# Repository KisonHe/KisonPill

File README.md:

# KisonPill

Use the switch at the bottom to choose serial download from cp2102 on board or ft2232.
R1 should be left not connected.

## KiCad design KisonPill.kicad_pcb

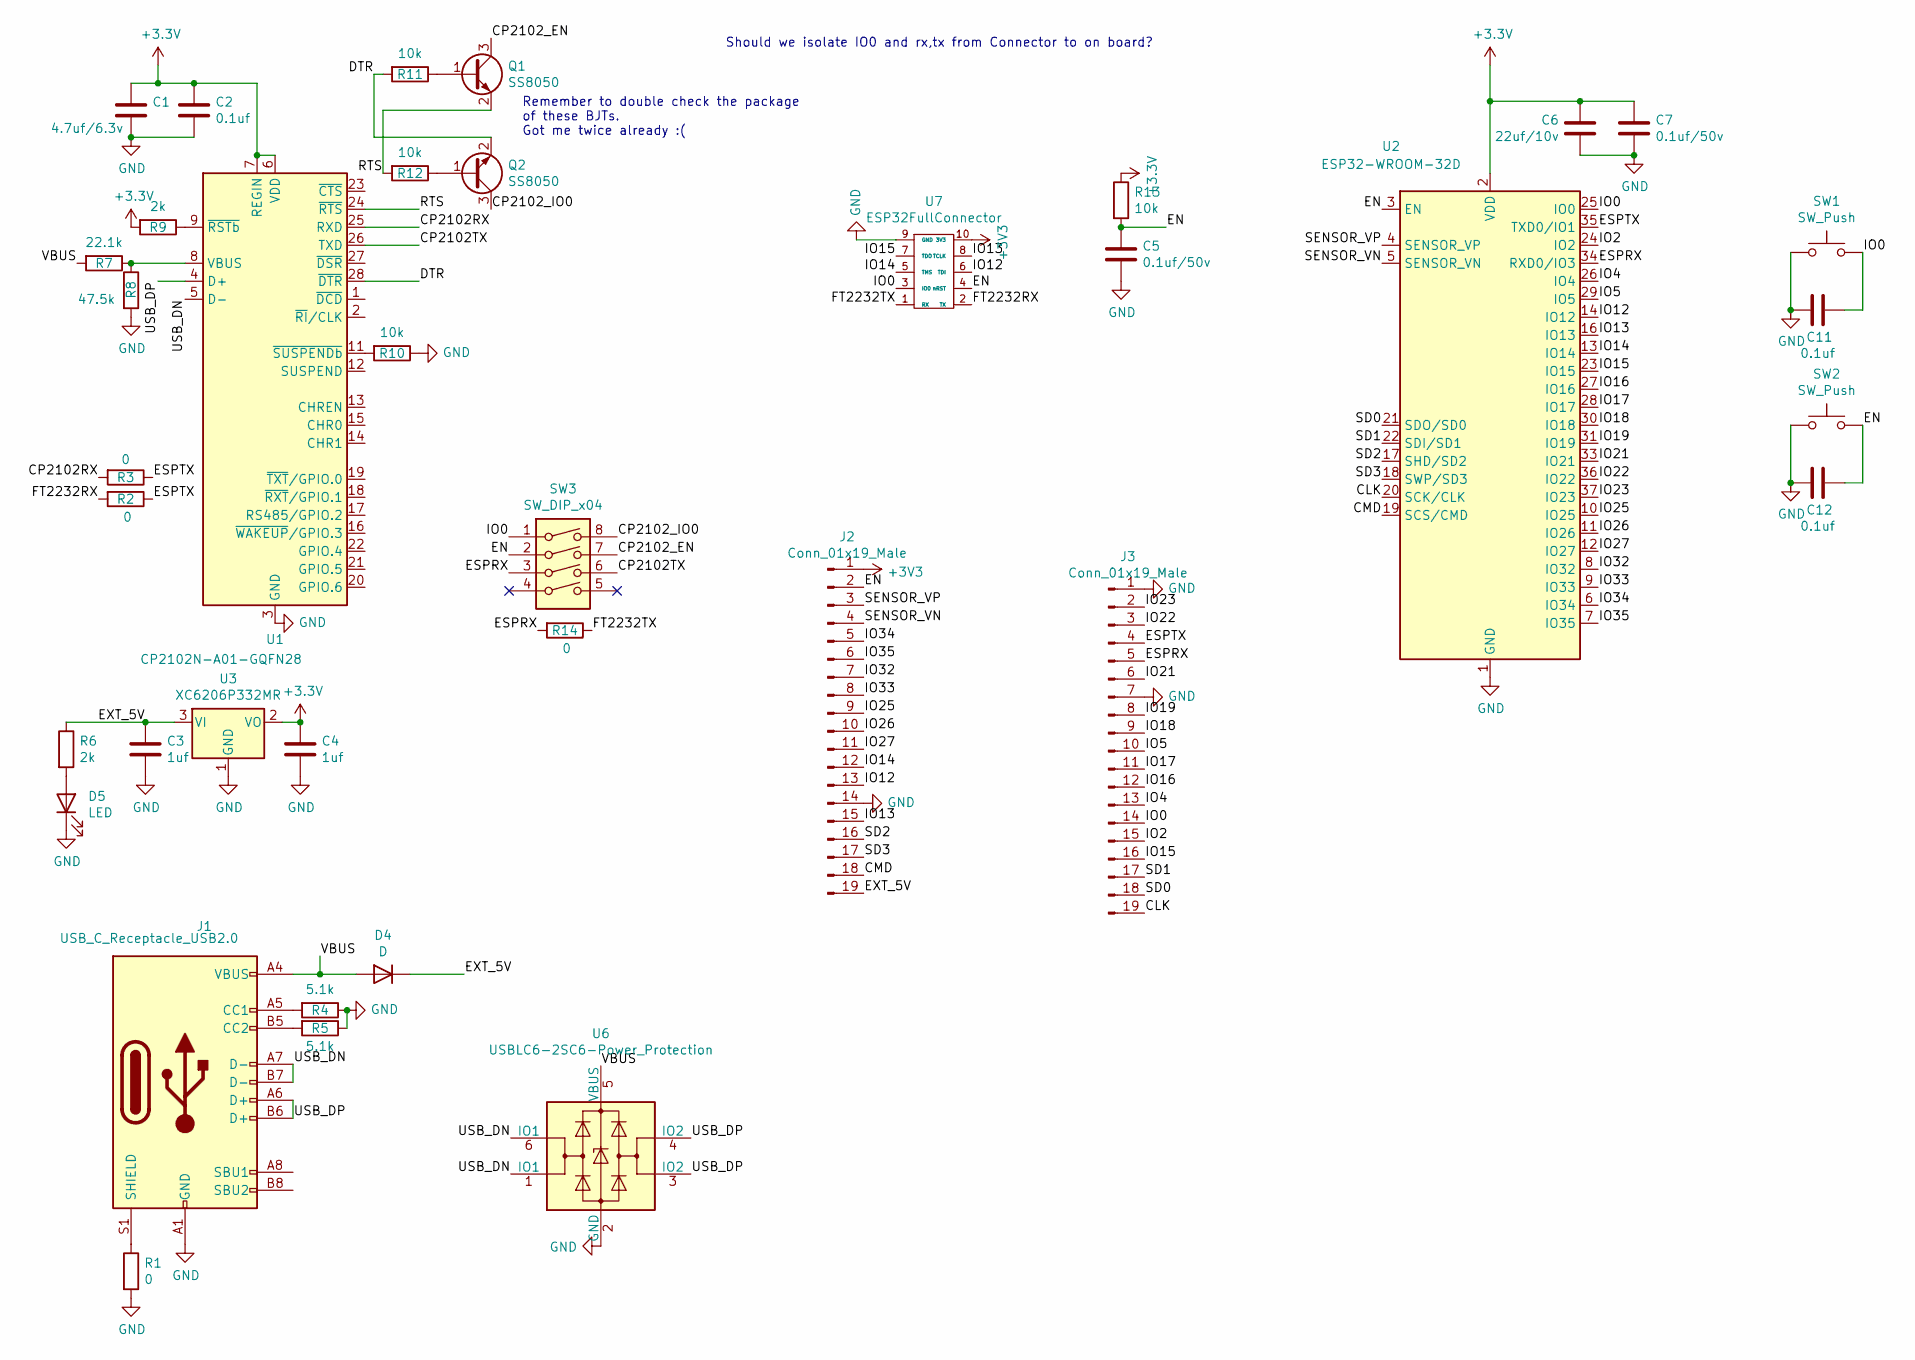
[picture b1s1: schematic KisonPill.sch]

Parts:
C1: 4.7uf/6.3v; C_0603_1608Metric; LCSC C907730
C2, C11, C12: 0.1uf; C_0603_1608Metric; LCSC C1688
C3, C4: 1uf; C_0603_1608Metric
C5, C7: 0.1uf/50v; C_0603_1608Metric; LCSC C1688
C6: 22uf/10v; C_1206_3216Metric; LCSC C319197
D4: D; D_SOD-323; LCSC C124187
D5: LED; LED_0603_1608Metric; LCSC C181863
J1: USB_C_Receptacle_USB2.0; USB_C_Receptacle_HRO_TYPE-C-31-M-12; LCSC C165948
J2, J3: Conn_01x19_Male; PinHeader_1x19_P2.54mm_Vertical
Q1, Q2: SS8050; SOT-23; LCSC C541705
R1, R2, R3, R14: 0; R_0603_1608Metric; LCSC C429667
R4, R5: 5.1k; R_0603_1608Metric; LCSC C325524
R6, R9: 2k; R_0603_1608Metric; LCSC C226705
R7: 22.1k; R_0603_1608Metric; LCSC C325588
R8: 47.5k; R_0603_1608Metric; LCSC C25896
R10, R11, R12, R13: 10k; R_0603_1608Metric; LCSC C149898
SW1, SW2: SW_Push; BTN-TS342A4P-WZ-C557592; LCSC C557592
SW3: SW_DIP_x04; SW_DIP_SPSTx04_Slide_Copal_CHS-04B_W7.62mm_P1.27mm
U1: CP2102N-A01-GQFN28; QFN-28-1EP_5x5mm_P0.5mm_EP3.35x3.35mm
U2: ESP32-WROOM-32D; ESP32-WROOM-32
U3: XC6206P332MR; SOT-23
U6: USBLC6-2SC6-Power_Protection; USBLC6-2P6-SOT666
U7: ESP32FullConnector; Molex_CLIK-Mate_502382-1070_1x10-1MP_P1.25mm_Vertical

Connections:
/CLK: J3.19, U2.20 (SCK/CLK)
/CMD: J2.18, U2.19 (SCS/CMD)
/CP2102RX: R3.2, U1.25 (RXD)
/CP2102TX: SW3.6, U1.26 (TXD)
/CP2102_EN: Q1.3 (C), SW3.7
/CP2102_IO0: Q2.3 (C), SW3.8
/DTR: Q2.2 (E), R11.2, U1.28 (~DTR)
/EN: C5.1, C12.2, J2.2, R13.2, SW2.2, SW3.2, U2.3 (EN), U7.4 (nRST)
/ESPRX: J3.5, R14.2, SW3.3, U2.34 (RXD0/IO3)
/ESPTX: J3.4, R2.1, R3.1, U2.35 (TXD0/IO1)
/EXT_5V: C3.1, D4.1 (K), J2.19, R6.1, U3.3 (VI)
/FT2232RX: R2.2, U7.2 (TX)
/FT2232TX: R14.1, U7.1 (RX)
/IO0: C11.2, J3.14, SW1.2, SW3.1, U2.25 (IO0), U7.3 (IO0)
/IO2: J3.15, U2.24 (IO2)
/IO4: J3.13, U2.26 (IO4)
/IO5: J3.10, U2.29 (IO5)
/IO12: J2.13, U2.14 (IO12), U7.6 (TDI)
/IO13: J2.15, U2.16 (IO13), U7.8 (TCLK)
/IO14: J2.12, U2.13 (IO14), U7.5 (TMS)
/IO15: J3.16, U2.23 (IO15), U7.7 (TDO)
/IO16: J3.12, U2.27 (IO16)
/IO17: J3.11, U2.28 (IO17)
/IO18: J3.9, U2.30 (IO18)
/IO19: J3.8, U2.31 (IO19)
/IO21: J3.6, U2.33 (IO21)
/IO22: J3.3, U2.36 (IO22)
/IO23: J3.2, U2.37 (IO23)
/IO25: J2.9, U2.10 (IO25)
/IO26: J2.10, U2.11 (IO26)
/IO27: J2.11, U2.12 (IO27)
/IO32: J2.7, U2.8 (IO32)
/IO33: J2.8, U2.9 (IO33)
/IO34: J2.5, U2.6 (IO34)
/IO35: J2.6, U2.7 (IO35)
/RTS: Q1.2 (E), R12.2, U1.24 (~RTS)
/SD0: J3.18, U2.21 (SDO/SD0)
/SD1: J3.17, U2.22 (SDI/SD1)
/SD2: J2.16, U2.17 (SHD/SD2)
/SD3: J2.17, U2.18 (SWP/SD3)
/SENSOR_VN: J2.4, U2.5 (SENSOR_VN)
/SENSOR_VP: J2.3, U2.4 (SENSOR_VP)
/USB_DN: J1.A7 (D-), J1.B7 (D-), U1.5 (D-), U6.1 (IO1), U6.6 (IO1)
/USB_DP: J1.A6 (D+), J1.B6 (D+), U1.4 (D+), U6.3 (IO2), U6.4 (IO2)
/VBUS: D4.2 (A), J1.A4 (VBUS), J1.A9 (VBUS), J1.B4 (VBUS), J1.B9 (VBUS), R7.2, U6.5 (VBUS)
GND: C1.2, C2.2, C3.2, C4.2, C5.2, C6.1, C7.2, C11.1, C12.1, D5.1 (K), J1.A1 (GND), J1.A12 (GND), J1.B1 (GND), J1.B12 (GND), J2.14, J3.1, J3.7, R1.2, R4.1, R5.1, R8.2, R10.1, SW1.1, SW2.1, U1.3 (GND), U1.29 (GND), U2.1 (GND), U2.15 (GND), U2.38 (GND), U2.39 (GND), U3.1 (GND), U6.2 (GND), U7.9 (GND)
unnamed: D5.2 (A), R6.2
unnamed: J1.A5 (CC1), R4.2
unnamed: J1.B5 (CC2), R5.2
unnamed: J1.S1 (SHIELD), R1.1
unnamed: Q1.1 (B), R11.1
unnamed: Q2.1 (B), R12.1
unnamed: R7.1, R8.1, U1.8 (VBUS)
unnamed: R9.1, U1.9 (~RSTb)
unnamed: R10.2, U1.11 (~SUSPENDb)

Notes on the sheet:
Should we isolate IO0 and rx,tx from Connector to on board?
Remember to double check the package of these BJTs. Got me twice already :(

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
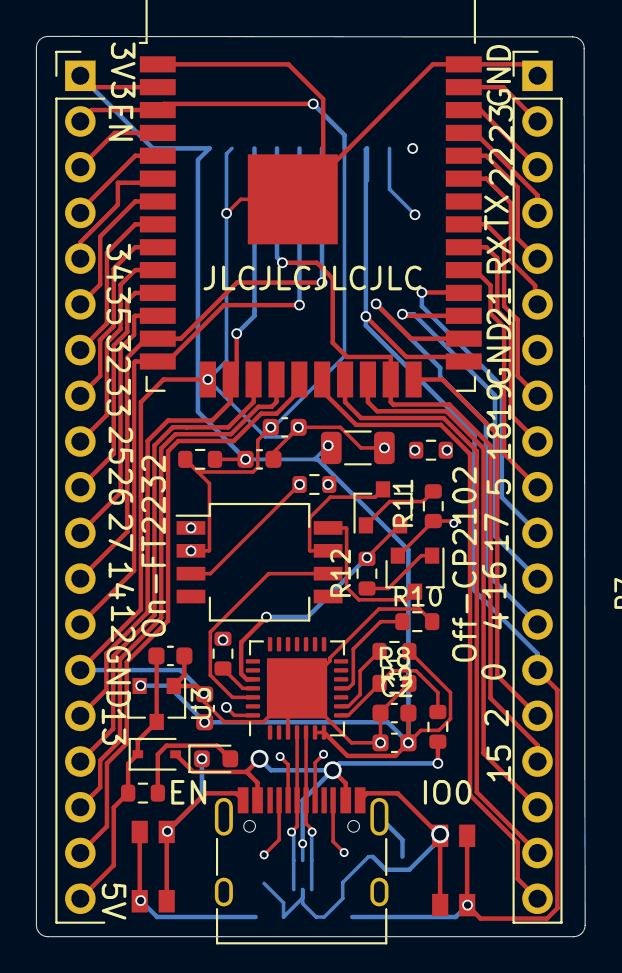
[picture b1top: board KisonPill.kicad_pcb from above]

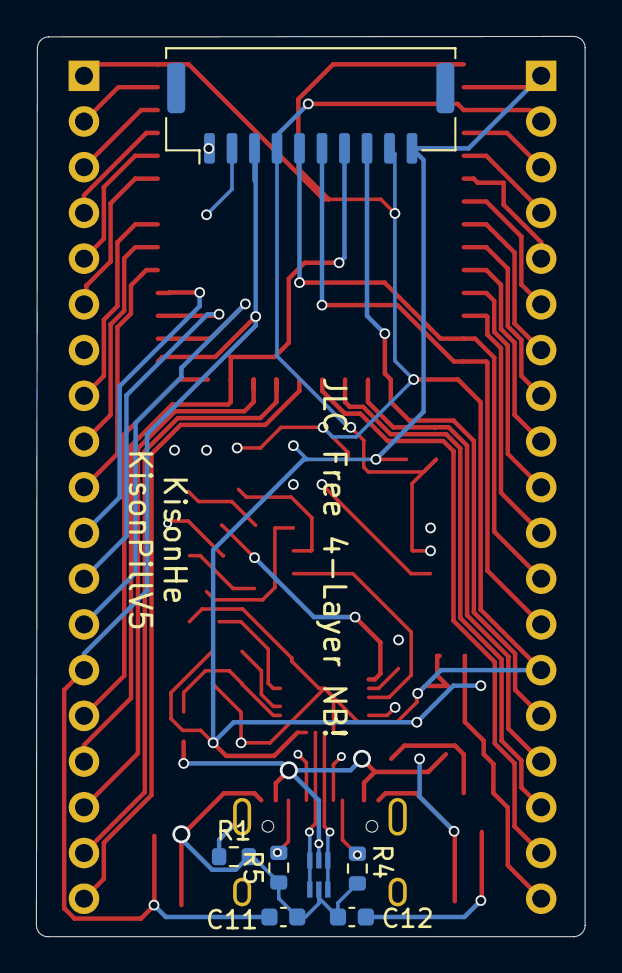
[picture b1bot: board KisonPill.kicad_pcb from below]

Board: 4 copper layers, 30.5 x 50.0 mm, 38 parts (7 on the bottom side), 56 nets.

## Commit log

2021-03-17 V0.1
2021-03-17 Add Elaina
2021-03-28 save
2021-04-06 Fix Error Over RX&TX
2021-04-07 Error Fix
2021-04-12 Improve Texts
2021-04-21 Added a switch to pick TX
2021-04-22 Fix Direction Errors
2021-04-29 Modify Button
2021-06-29 V5
    Fix BJT package bug :(
